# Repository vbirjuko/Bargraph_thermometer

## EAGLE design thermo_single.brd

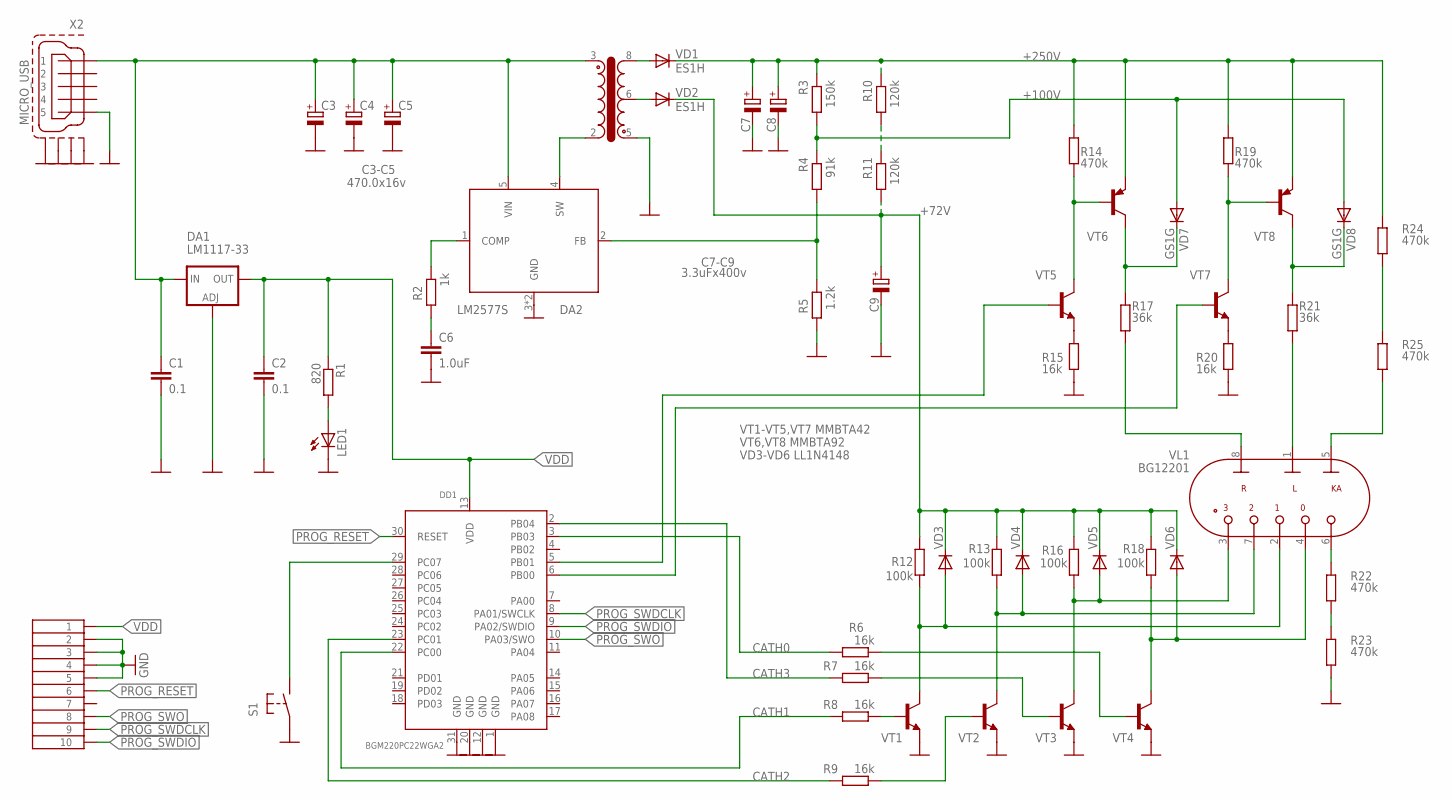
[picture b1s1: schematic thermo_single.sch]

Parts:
C1, C2: 0.1; C0805
C3, C4, C5: 470.0x16v; PANASONIC_G
C6: 1.0uF; C1206
C7, C8, C9: 3.3uFx400v; PANASONIC_G
DA1: LM1117-33; SOT223
DA2: LM2577S; TO263-5
DD1: BGM220PC22WGA2; BGM13P22F512GEV2
LED1: LEDP-LCC-2; P-LCC-2
R1: 820; R0805
R2: 1k; R0805
R3: 150k; R0805
R4: 91k; R0805
R5: 1.2k; R0805
R6, R7, R8, R9, R15, R20: 16k; R0805
R10, R11: 120k; R0805
R12, R13, R16, R18: 100k; R0805
R14, R19, R22, R23, R24, R25: 470k; R0805
R17, R21: 36k; R0805
S1: 10-XXPTS636SJ25; PTS636SJ25
T1: TRANSFFB; EFD20-8
VD1, VD2: ES1H; DO-214AC
VD3, VD4, VD5, VD6: LL4148; SOD80C
VD7, VD8: GS1G; DO-214AC
VL1: BG12201
VT1, VT2, VT3, VT4, VT5, VT7: mmbta42; SOT23-BEC
VT6, VT8: mmbta92; SOT23-BEC
X1: PINHEAD2X5; DS1031-08-2*5P8BS-4-1
X2: MICRO_USB; MICRO_USB_MOLEX

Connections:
+5V: C1.1, C3.+, C4.+, C5.+, DA1.3 (IN), DA2.5 (VIN), T1.3, X2.1
+72V: C9.+, R11.2, R12.2, R13.2, R16.2, R18.2, VD2.1 (C), VD3.C, VD4.C, VD5.C, VD6.C
+100V: R3.2, R4.1, VD7.2 (A), VD8.2 (A)
+250V: C7.+, C8.+, R3.1, R10.1, R14.2, R19.2, R24.2, VD1.1 (C), VT6.E, VT8.E
ANODE0: DD1.5 (PB01), VT5.B
ANODE1: DD1.6 (PB00), VT7.B
CATH0: DD1.3 (PB03), R6.2
CATH1: DD1.22 (PC00), R8.2
CATH2: DD1.23 (PC01), R9.2
CATH3: DD1.2 (PB04), R7.2
CH1ANODE: R21.1, VL1.1 (LA)
CH2ANODE: R17.1, VL1.8 (RA)
GND: C1.2, C2.2, C3.-, C4.-, C5.-, C6.2, C7.-, C8.-, C9.-, DA1.1 (ADJ), DA2.3 (GND), DA2.6 (GND), DD1.1 (GND), DD1.12 (GND), DD1.20 (GND), DD1.31 (GND), LED1.C, R5.2, R15.1, R20.1, R23.1, S1.P$1, T1.5, VT1.E, VT2.E, VT3.E, VT4.E, X1.2, X1.3, X1.4, X1.5, X2.5, X2.P$1 (S1), X2.P$2 (S2), X2.P$4 (S3), X2.P$5 (S4)
KA_ANODE: R25.1, VL1.5 (KA_A)
KEY: DD1.29 (PC07), S1.P$2 (S)
unnamed: DA2.4 (SW), T1.2
unnamed: R22.2, VL1.6 (KA_C)
unnamed: R22.1, R23.2
unnamed: DA2.2 (FB), R4.2, R5.1
unnamed: C6.1, R2.2
unnamed: DA2.1 (COMP), R2.1
unnamed: R15.2, VT5.E
unnamed: R20.2, VT7.E
unnamed: R14.1, VT5.C, VT6.B
unnamed: R10.2, R11.1
unnamed: R19.1, VT7.C, VT8.B
unnamed: R8.1, VT1.B
unnamed: R7.1, VT3.B
unnamed: R6.1, VT4.B
unnamed: R9.1, VT2.B
unnamed: R17.2, VD7.1 (C), VT6.C
unnamed: R21.2, VD8.1 (C), VT8.C
unnamed: T1.6, VD2.2 (A)
unnamed: T1.8, VD1.2 (A)
unnamed: R24.1, R25.2
unnamed: LED1.A, R1.2
PH1CATHODE: R12.1, VD3.A, VL1.2 (C1), VT1.C
PH2CATHODE: R13.1, VD4.A, VL1.7 (C2), VT2.C
PH3CATHODE: R16.1, VD5.A, VL1.3 (C3), VT3.C
PROG_RESET: DD1.30 (RESET), X1.6
PROG_SWDCLK: DD1.8 (PA01/SWCLK), X1.9
PROG_SWDIO: DD1.9 (PA02/SWDIO), X1.10
PROG_SWO: DD1.10 (PA03/SWO), X1.8
RESETCATHODE: R18.1, VD6.A, VL1.4 (CR), VT4.C
VDD: C2.1, DA1.4 (OUT), DD1.13 (VDD), R1.1, X1.1

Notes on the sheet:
C3-C5
VT1-VT5,VT7 MMBTA42
VT6,VT8 MMBTA92
C7-C9
VD3-VD6 LL1N4148

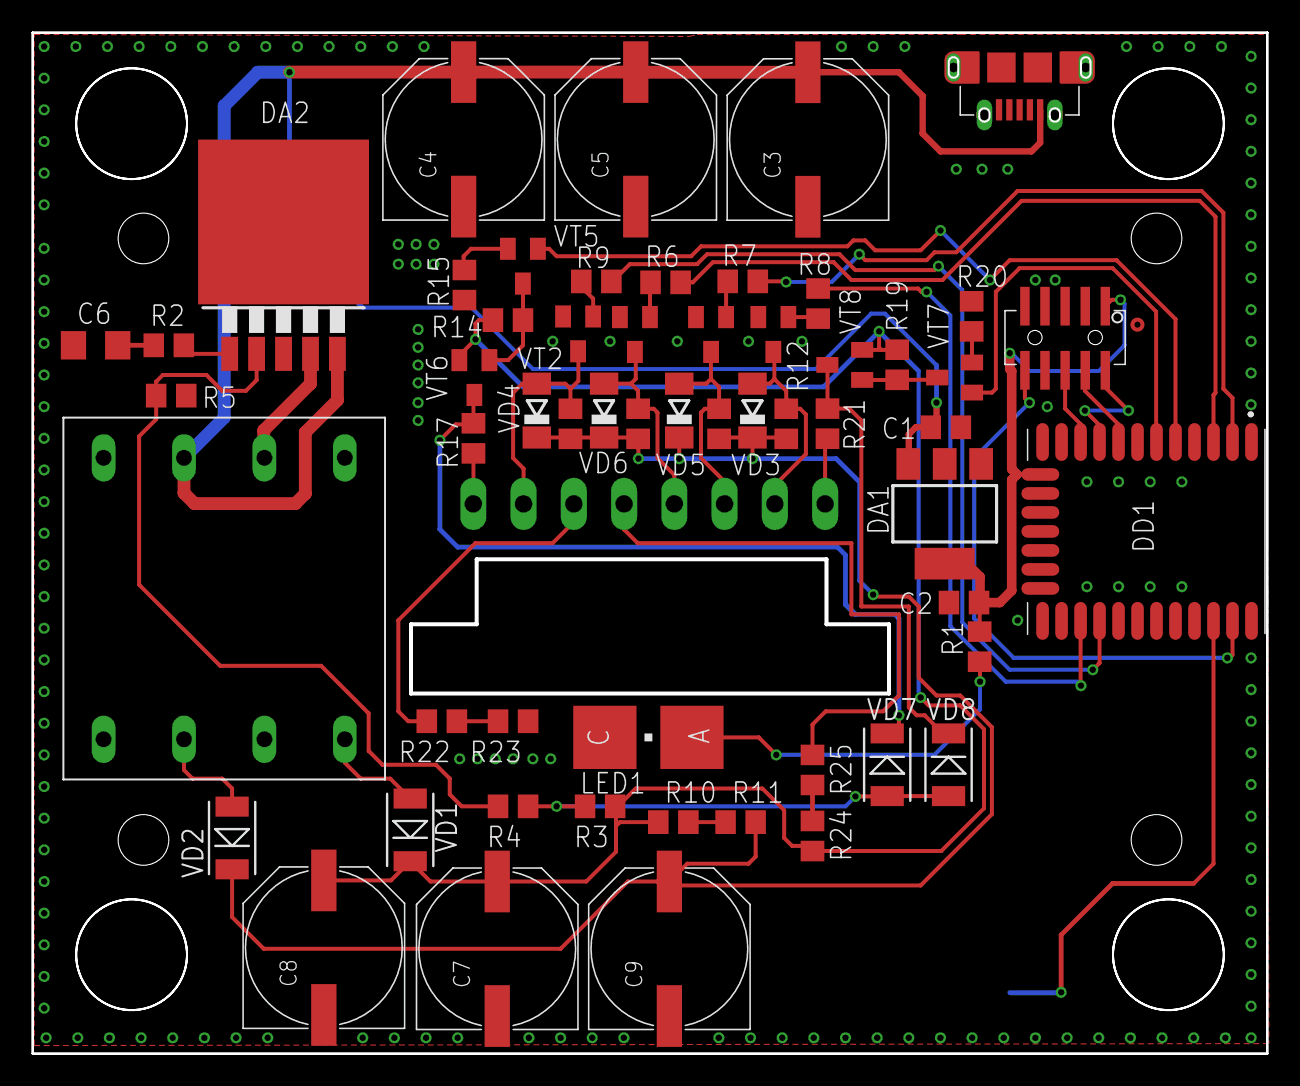
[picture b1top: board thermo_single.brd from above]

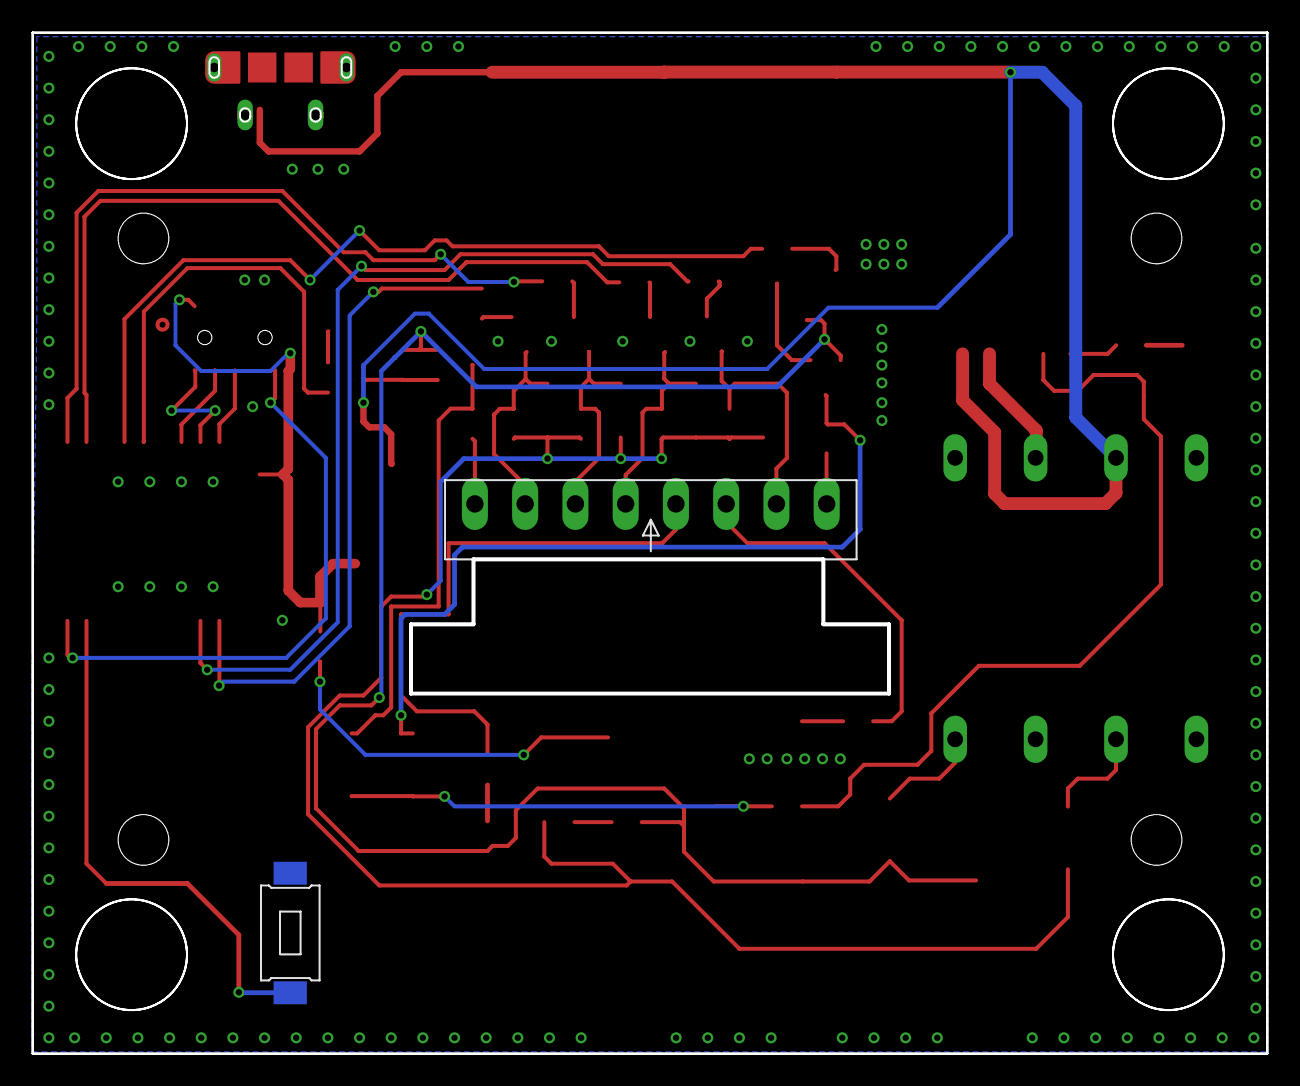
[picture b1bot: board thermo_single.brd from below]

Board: 2 copper layers, 77.9 x 64.4 mm, 61 parts (2 on the bottom side), 45 nets.

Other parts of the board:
U$1, U$5: 50-200-11

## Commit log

2021-11-18 Rename common/bargraph_therm.slcp to commonbargraph_therm.slcp
2021-11-18 Rename commonbargraph_therm.slcp to bargraph_therm.slcp
2021-11-18 Rename common/.cproject to .cproject
2021-11-18 Rename common/.project to .project
2021-11-18 Rename common/bargraph_therm.pintool to bargraph_therm.pintool
2021-11-24 Rename btconf/gatt_configuration.btconf to config/btconf/gatt_configuration.btconf
